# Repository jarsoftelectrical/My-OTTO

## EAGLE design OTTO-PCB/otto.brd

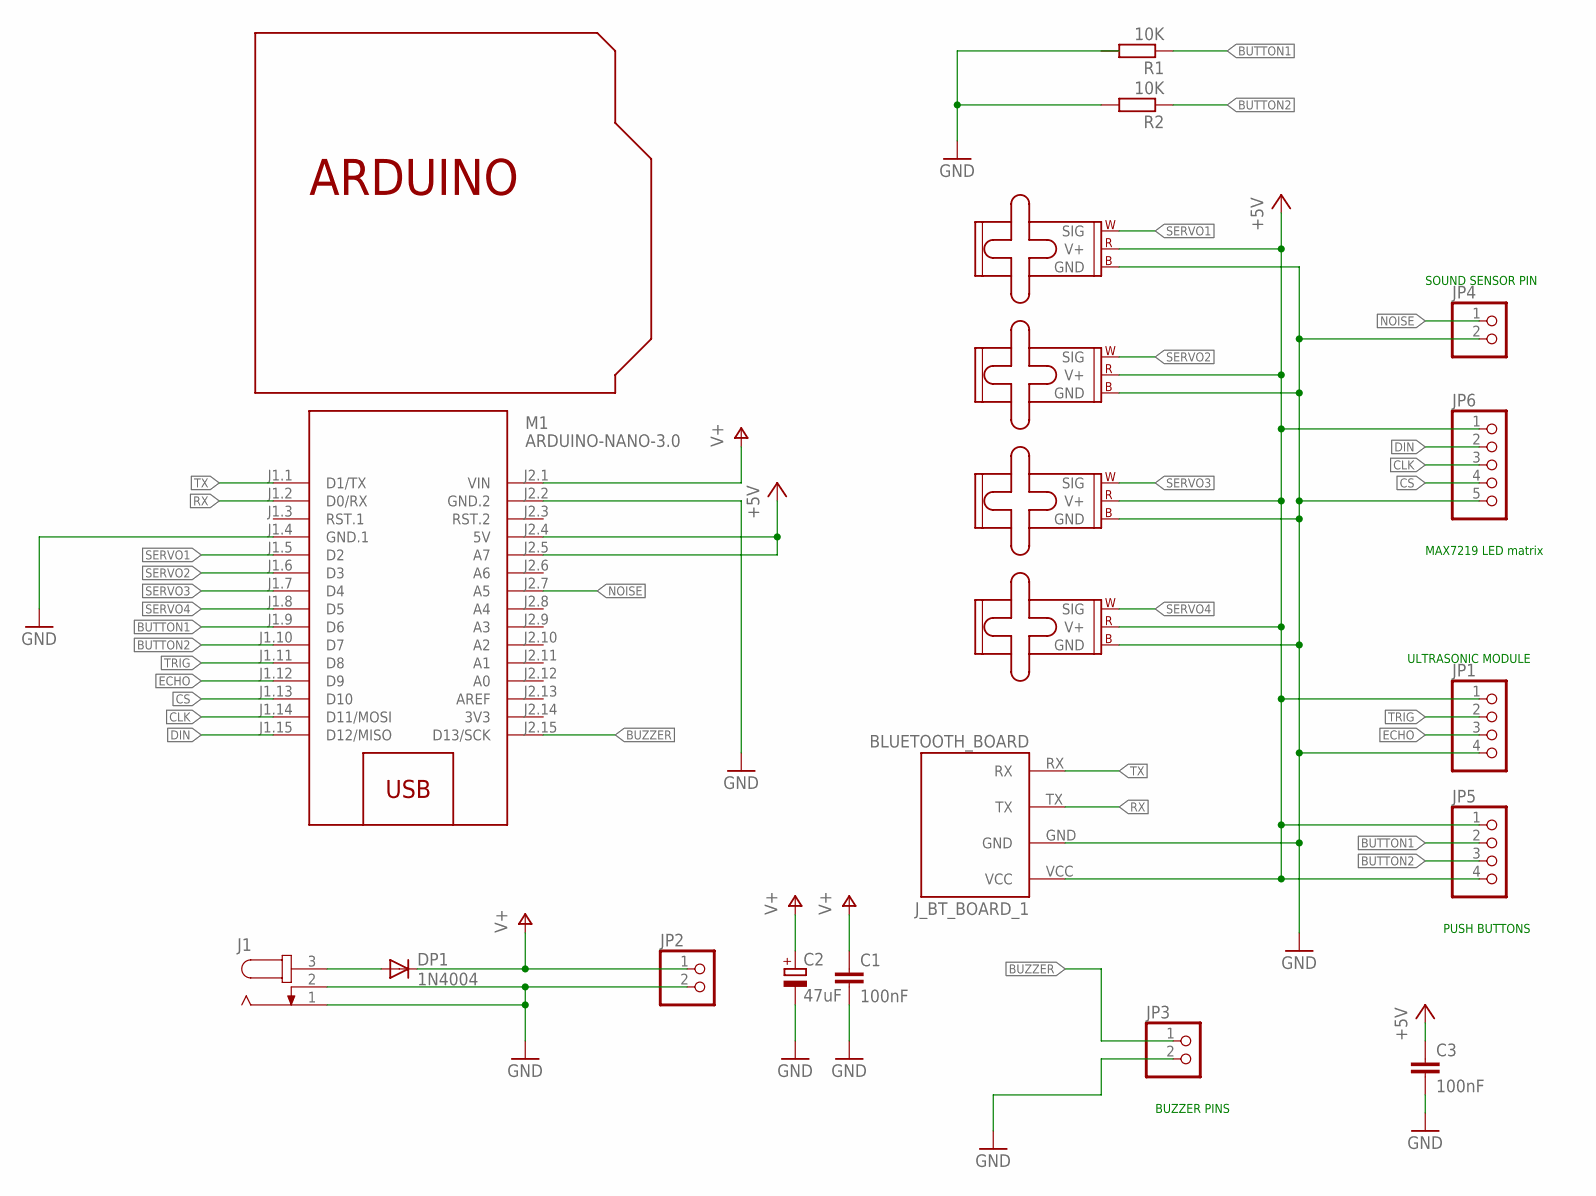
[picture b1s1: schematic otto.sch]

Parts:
C1, C3: 100nF; C025-025X050
C2: 47uF; 140CLH-0810
DP1: 1N4004; DO41-10
J1: JACK-PLUG0; SPC4077
JP1, JP5: PINHD-1X4; 1X04
JP2, JP3, JP4: PINHD-1X2; 1X02
JP6: PINHD-1X5; 1X05
J_BT_BOARD_1: BLUETOOTH_BOARD; BT_BOARD_FOOTPRINT
M1: ARDUINO-NANO-3.0
M2, M3, M4, M5: SMALL_SERVO; 1X03
R1, R2: 10K; 0207/7
U$1: SHIELDSMALL; ARDUINOSHIELDSMALL

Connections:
3V3: M1.J2.14 (3V3)
+5V: C3.1, JP1.1, JP5.1, JP5.4, JP6.1, J_BT_BOARD_1.VCC, M1.J2.4 (5V), M1.J2.5 (A7), M2.2 (V+), M3.2 (V+), M4.2 (V+), M5.2 (V+)
BUTTON1: JP5.2, M1.J1.9 (D6), R1.1
BUTTON2: JP5.3, M1.J1.10 (D7), R2.1
BUZZER: JP3.1, M1.J2.15 (D13/SCK)
CLK: JP6.3, M1.J1.14 (D11/MOSI)
CS: JP6.4, M1.J1.13 (D10)
DIN: JP6.2, M1.J1.15 (D12/MISO)
ECHO: JP1.3, M1.J1.12 (D9)
GND: C1.2, C2.-, C3.2, J1.1, J1.2, JP1.4, JP2.2, JP3.2, JP4.2, JP6.5, J_BT_BOARD_1.GND, M1.J1.4 (GND.1), M1.J2.2 (GND.2), M2.3 (GND), M3.3 (GND), M4.3 (GND), M5.3 (GND), R2.2
unnamed: DP1.A, J1.3
NOISE: JP4.1, M1.J2.7 (A5)
RX: J_BT_BOARD_1.TX, M1.J1.2 (D0/RX)
SERVO1: M1.J1.5 (D2), M2.1 (SIG)
SERVO2: M1.J1.6 (D3), M3.1 (SIG)
SERVO3: M1.J1.7 (D4), M4.1 (SIG)
SERVO4: M1.J1.8 (D5), M5.1 (SIG)
TRIG: JP1.2, M1.J1.11 (D8)
TX: J_BT_BOARD_1.RX, M1.J1.1 (D1/TX)
V+: C1.1, C2.+, DP1.C, JP2.1, M1.J2.1 (VIN)

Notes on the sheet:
MAX7219 LED matrix
ULTRASONIC MODULE
PUSH BUTTONS
SOUND SENSOR PIN
BUZZER PINS

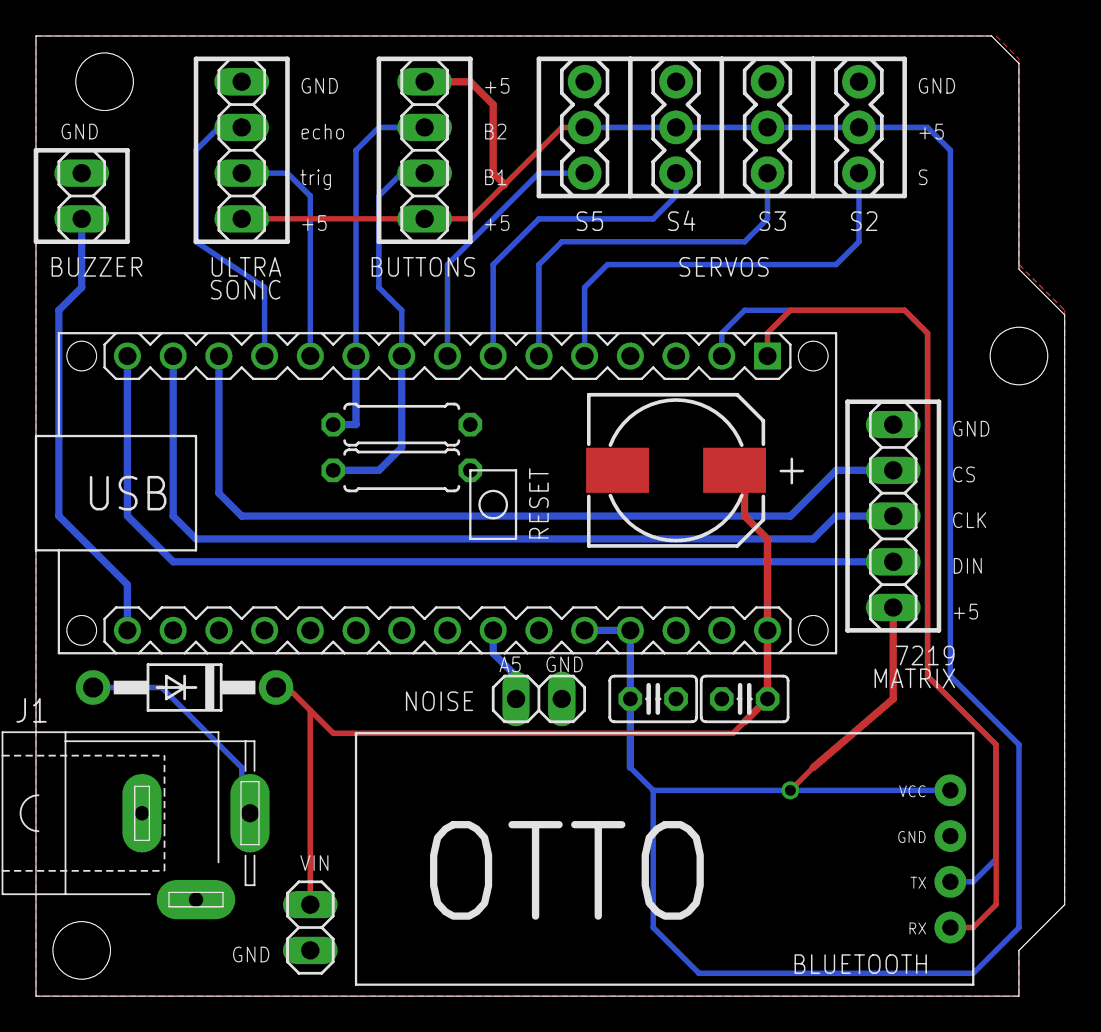
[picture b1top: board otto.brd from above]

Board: 2 copper layers, 57.2 x 53.3 mm, 20 parts (0 on the bottom side), 19 nets.

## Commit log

2017-02-09 :lollipop: Added .gitattributes & .gitignore files
2017-02-14 Create Read me
2017-02-17 Add files via upload
    Modified STLs for LED MATRIX and PUSH BUTTONS

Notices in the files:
parts and their libraries:
diy-modules: Released under the Creative Commons Attribution 4.0 International License: http://creativecommons.org/licenses/by/4.0
SparkFun-Electromechanical: Licensing: CC v3.0 Share-Alike You are welcome to use this library for commercial purposes.
